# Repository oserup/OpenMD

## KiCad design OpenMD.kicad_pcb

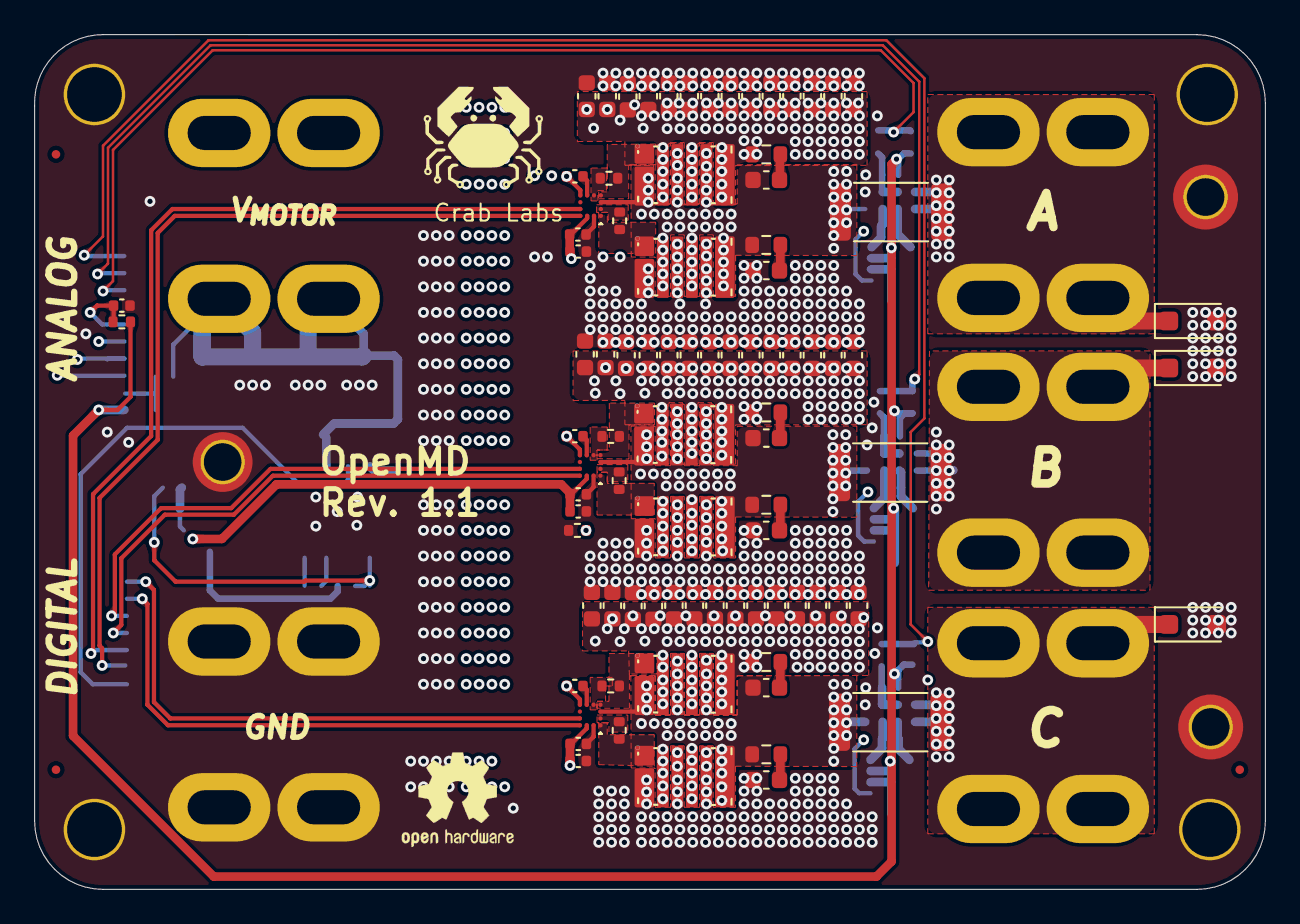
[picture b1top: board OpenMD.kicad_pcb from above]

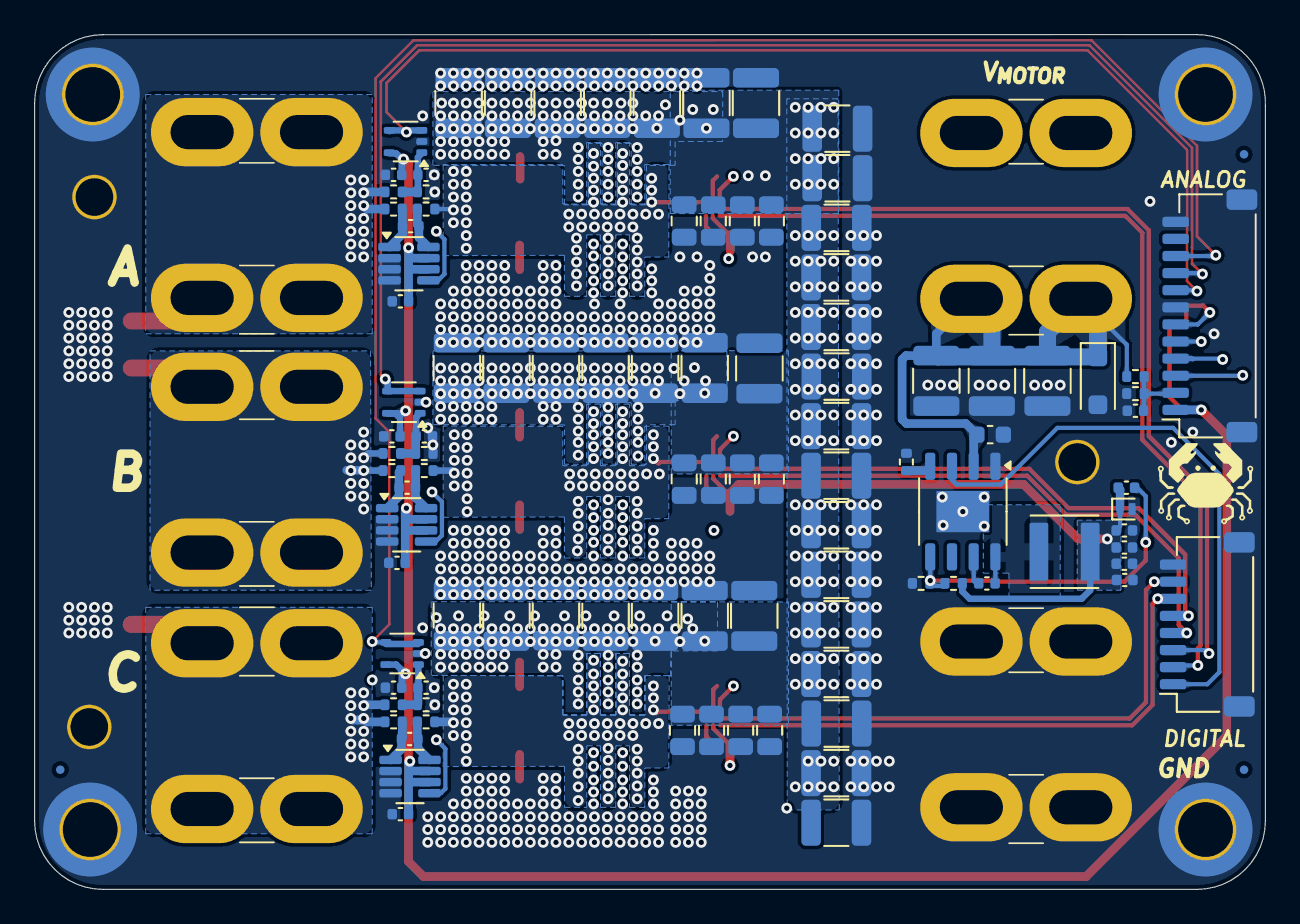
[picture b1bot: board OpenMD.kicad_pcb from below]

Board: 6 copper layers, 72.0 x 50.0 mm, 206 parts (112 on the bottom side), 59 nets.

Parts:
C1, C2, C3, C6, C7, C8, C9, C12, C15, C18, C19, C21, C23, C24, C26, C27, C78, C79, C80, C81, C82, C86, C87, C88, C89, C91, C93, C94, C98, C99, C100, C101, C102, C103, C104, C105, C106, C107, C108: 10uF; C_1210_3225Metric
C4, C5, C10, C13, C14, C16, C17, C20, C22, C25, C30, C33, C36, C46, C48, C50, C51, C53, C55, C58, C60, C62, C70, C71, C72, C73, C74, C75, C109, C110, C111, C112, C113, C114, C115, C116, C117, C118, C119, C120, C121, C122, C123: 100nF; C_0603_1608Metric
C11, C38, C39, C41, C42, C44, C45, C47, C49, C52, C54, C57, C59, C63, C77: 100nF; C_0402_1005Metric
C28, C29, C31, C32, C34, C35, C124, C125, C126, C127, C128, C129: 1uF; C_0805_2012Metric
C37, C40, C43, C64, C65, C90: 4.7uF; C_0402_1005Metric
C56, C61, C66, C83, C84, C85: C; C_0603_1608Metric
C67, C68, C69, C95, C96, C97: 10nF; C_0402_1005Metric
C76: 2.2nF; C_0402_1005Metric
C92: 20pF; C_0402_1005Metric
D7, D8, D9, D19: 100V; D_SOD-123F
D18: 6V; D_SOD-882
FID1, FID2, FID3, FID4, FID5, FID6: Fiducial; Fiducial_0.5mm_Mask1mm
H1, H2, H3, H4: M3; MountingHole_3.2mm_M3_ISO14580_Pad_TopOnly
H5: M2; MountingHole_2.2mm_M2_ISO7380_Pad_TopOnly
H6, H7: M2; MountingHole_2.2mm_M2_DIN965_Pad_TopOnly
J1: GND; DIP-4_252
J2: Digital; JST_SH_SM08B-SRSS-TB_1x08-1MP_P1.00mm_Horizontal
J3: Analog; JST_SH_SM12B-SRSS-TB_1x12-1MP_P1.00mm_Horizontal
J5: A; DIP-4_252
J6: B; DIP-4_252
J7: C; DIP-4_252
J8: V_{MOTOR}; DIP-4_252
L1: 68uH; L_Abracon_ASPI-4030S
Q1, Q2, Q3, Q4, Q5, Q6: EPC2361; D0606F_100V
R1, R4, R6, R9, R11, R14: 1; R_0402_1005Metric
R5, R16, R18, R20, R32: 240k; R_0402_1005Metric
R10: 72k; R_0402_1005Metric
R15: 27k; R_0402_1005Metric
R17, R19, R21, R31, R34: 10k; R_0402_1005Metric
R22, R24, R25, R27, R28, R30: 10; R_0402_1005Metric
R23, R26, R29: .5m; R_2512_6332Metric
R38, R39, R40, R41, R42, R43: R; R_0603_1608Metric
SYM1: Logo_Open_Hardware_Large; OSHW-Logo2_7.3x6mm_SilkScreen
TH1: 10k NTC; R_0402_1005Metric
U1, U2, U3: UP1966E; WLCSP1.6x1.6-12B_ECC
U4: LM5164DDA; HSOP-8-1EP_3.9x4.9mm_P1.27mm_EP2.41x3.1mm_ThermalVias
U5, U6, U7: OPA310xDCK; SOT-353_SC-70-5
U8, U9, U10: INA241A2; SOT-23-8

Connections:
/A: D7.1 (K), J5.1, R16.1, R23.2, R24.1
/AH: Q4.1 (G), R4.2, U1.D1 (UGL)
/AL: Q1.1 (G), R1.2, U1.A1 (LGL)
/B: D8.1 (K), J6.1, R18.1, R26.2, R27.1
/BH: Q5.1 (G), R9.2, U2.D1 (UGL)
/BL: Q2.1 (G), R6.2, U2.A1 (LGL)
/C: D9.1 (K), J7.1, R20.1, R29.2, R30.1
/CH: Q6.1 (G), R14.2, U3.D1 (UGL)
/CL: Q3.1 (G), R11.2, U3.A1 (LGL)
/DRV_TEMP_SENSE: C77.1, J3.6, R34.2, TH1.1
/ENABLE: J2.1, U4.3 (EN/UVLO)
/GND: C1.2, C2.2, C3.2, C4.2, C5.2, C6.2, C7.2, C8.2, C9.2, C10.2, C11.2, C12.2, C13.2, C14.2, C15.2, C16.2, C17.2, C18.2, C19.2, C20.2, C21.2, C22.2, C23.2, C24.2, C25.2, C26.2, C27.2, C28.2, C29.2, C30.2, C31.2, C32.2, C33.2, C34.2, C35.2, C36.2, C37.2, C38.2, C40.2, C41.2, C43.2, C44.2, C46.2, C47.2, C48.2, C50.2, C51.2, C52.2, C53.2, C55.2, C57.2, C58.2, C60.2, C62.2, C63.2, C64.2, C65.2, C67.2, C68.2, C69.2, C70.2, C71.2, C72.2, C73.2, C74.2, C75.2, C77.2, C78.2, C79.2, C80.2, C81.2, C82.2, C83.2, C84.2, C85.2, C86.2, C87.2, C88.2, C89.2, C90.2, C91.2, C93.2, C94.2, C95.2, C96.2, C97.2, C98.2, C99.2, C100.2, C101.2, C102.2, C103.2, C104.2, C105.2, C106.2, C107.2, C108.2, C109.2, C110.2, C111.2, C112.2, C113.2, C114.2, C115.2, C116.2, C117.2, C118.2, C119.2, C120.2, C121.2, C122.2, C123.2, C124.2, C125.2, C126.2, C127.2, C128.2, C129.2, D7.2 (A), D8.2 (A), D9.2 (A), D18.2 (A), D19.2 (A), H1.1, H2.1, H3.1, H4.1, H5.1, H6.1, H7.1, J1.1, J2.8, J2.MP (MountPin), J3.7, J3.12, J3.MP (MountPin), Q1.2 (S), Q1.4 (S), Q1.6 (S), Q2.2 (S), Q2.4 (S), Q2.6 (S), Q3.2 (S), Q3.4 (S), Q3.6 (S), R10.2, R15.2, R17.2, R19.2, R21.2, R31.2, TH1.2, U1.A2 (GND), U2.A2 (GND), U3.A2 (GND), U4.1 (GND), U4.9 (EP), U5.2 (V-), U6.2 (V-), U7.2 (V-), U8.2 (GND), U8.3 (REF2), U8.4 (GND), U9.2 (GND), U9.3 (REF2), U9.4 (GND), U10.2 (GND), U10.3 (REF2), U10.4 (GND)
/INPUT.AH: J2.3, U1.B4 (HI)
/INPUT.AL: J2.2, U1.A4 (LI)
/INPUT.BH: J2.5, U2.B4 (HI)
/INPUT.BL: J2.4, U2.A4 (LI)
/INPUT.CH: J2.7, U3.B4 (HI)
/INPUT.CL: J2.6, U3.A4 (LI)
/I_SENSE.A: J3.3, U8.5
/I_SENSE.B: J3.4, U9.5
/I_SENSE.C: J3.5, U10.5
/Phase Current Sensors/Current Sense A/V+: C49.1, R22.2, U8.8 (+)
/Phase Current Sensors/Current Sense A/V-: C49.2, R24.2, U8.1 (-)
/Phase Current Sensors/Current Sense B/V+: C54.1, R25.2, U9.8 (+)
/Phase Current Sensors/Current Sense B/V-: C54.2, R27.2, U9.1 (-)
/Phase Current Sensors/Current Sense C/V+: C59.1, R28.2, U10.8 (+)
/Phase Current Sensors/Current Sense C/V-: C59.2, R30.2, U10.1 (-)
/Predriver Voltage Supply/FB: C92.2, R5.2, R10.1, U4.5 (FB)
/Predriver Voltage Supply/SW: C76.2, L1.1, U4.8 (SW)
/Predrivers/Gate Driver A/BOOT: C39.1, U1.D3 (BOOT)
/Predrivers/Gate Driver A/UGH: R4.1, U1.D2 (UGH)
/Predrivers/Gate Driver B/BOOT: C42.1, U2.D3 (BOOT)
/Predrivers/Gate Driver B/UGH: R9.1, U2.D2 (UGH)
/Predrivers/Gate Driver C/BOOT: C45.1, U3.D3 (BOOT)
/Predrivers/Gate Driver C/UGH: R14.1, U3.D2 (UGH)
/SW.A: C39.2, C56.2, Q1.3 (D), Q1.5 (D), Q1.7 (D), Q4.2 (S), Q4.4 (S), Q4.6 (S), R22.1, R23.1, R41.1, U1.C1 (PHASE), U1.D4 (PHASE)
/SW.B: C42.2, C61.2, Q2.3 (D), Q2.5 (D), Q2.7 (D), Q5.2 (S), Q5.4 (S), Q5.6 (S), R25.1, R26.1, R42.1, U2.C1 (PHASE), U2.D4 (PHASE)
/SW.C: C45.2, C66.2, Q3.3 (D), Q3.5 (D), Q3.7 (D), Q6.2 (S), Q6.4 (S), Q6.6 (S), R28.1, R29.1, R43.1, U3.C1 (PHASE), U3.D4 (PHASE)
/V_SENSE: C63.1, J3.2, R31.1, R32.2
/V_SENSE.A: J3.8, U5.3 (-), U5.4
/V_SENSE.B: J3.9, U6.3 (-), U6.4
/V_SENSE.C: J3.10, U7.3 (-), U7.4
/V_{ANA}: C47.1, C52.1, C57.1, C95.1, C96.1, C97.1, J3.1, R34.1, U5.5 (V+), U6.5 (V+), U7.5 (V+), U8.6 (V+), U8.7 (REF1), U9.6 (V+), U9.7 (REF1), U10.6 (V+), U10.7 (REF1)
/V_{DRV}: C11.1, C37.1, C38.1, C40.1, C41.1, C43.1, C44.1, C64.1, C65.1, C90.1, C92.1, D18.1 (K), L1.2, R5.1, U1.A3 (VCC), U2.A3 (VCC), U3.A3 (VCC)
/V_{MOTOR}: C1.1, C2.1, C3.1, C4.1, C5.1, C6.1, C7.1, C8.1, C9.1, C10.1, C12.1, C13.1, C14.1, C15.1, C16.1, C17.1, C18.1, C19.1, C20.1, C21.1, C22.1, C23.1, C24.1, C25.1, C26.1, C27.1, C28.1, C29.1, C30.1, C31.1, C32.1, C33.1, C34.1, C35.1, C36.1, C46.1, C48.1, C50.1, C51.1, C53.1, C55.1, C58.1, C60.1, C62.1, C70.1, C71.1, C72.1, C73.1, C74.1, C75.1, C78.1, C79.1, C80.1, C81.1, C82.1, C86.1, C87.1, C88.1, C89.1, C91.1, C93.1, C94.1, C98.1, C99.1, C100.1, C101.1, C102.1, C103.1, C104.1, C105.1, C106.1, C107.1, C108.1, C109.1, C110.1, C111.1, C112.1, C113.1, C114.1, C115.1, C116.1, C117.1, C118.1, C119.1, C120.1, C121.1, C122.1, C123.1, C124.1, C125.1, C126.1, C127.1, C128.1, C129.1, D19.1 (K), J8.1, Q4.3 (D), Q4.5 (D), Q4.7 (D), Q5.3 (D), Q5.5 (D), Q5.7 (D), Q6.3 (D), Q6.5 (D), Q6.7 (D), R32.1, R38.1, R39.1, R40.1, U4.2 (VIN)
unnamed: C56.1, R38.2
unnamed: C61.1, R39.2
unnamed: C66.1, R40.2
unnamed: C83.1, R41.2
unnamed: C84.1, R42.2
unnamed: C85.1, R43.2
unnamed: R1.1, U1.B1 (LGH)
unnamed: R6.1, U2.B1 (LGH)
unnamed: R11.1, U3.B1 (LGH)
unnamed: C76.1, U4.7 (BST)
unnamed: R15.1, U4.4 (RON)
unnamed: C67.1, R16.2, R17.1, U5.1 (+)
unnamed: C68.1, R18.2, R19.1, U6.1 (+)
unnamed: C69.1, R20.2, R21.1, U7.1 (+)

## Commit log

2025-01-06 adjustments

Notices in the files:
OpenMD.kicad_pcb:
License: CERN-OHL-W-2.0
